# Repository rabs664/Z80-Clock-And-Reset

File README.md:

# Z80-Clock-And-Reset
Simple 555 based astable and monostable clock and reset board.

The Z80 Clock and Reset board provides a variable astable clock where the frequency can be controlled by R8 or a monostable clock to allow the clock to be "single-stepped". The switch S1 toggles between the astable and monostable clock. Additional the switch S3 provides a reset signal for use with the Z80. 

Astable Clock Output

## Objective
Support Z80 CPU learning, specifically used with associated Z80 CPU Boards.

## Background
Used extensively during early Z80 learning to single step the clock or slow run the clock and watch the Z80 activity.

## Testing
The Z80 Clock and Reset V1.2 board has been built and tested. 

## PCBs
Gerber files are available in Code.

## Components
This [Digi-Key List](https://www.digikey.co.uk/en/mylists/list/MAI0B51H04) contains all components.

## Resources
[Zed80 Website](http://zed80.com/Z80-RETRO/index_Home.html)

[Ben Eater Clock](https://eater.net/8bit/clock)

## Acknowledgements
Don Prefontaine 

Peter Murray

[Ben Eater](https://eater.net)

# Release History
## Version 1.2
* First Release

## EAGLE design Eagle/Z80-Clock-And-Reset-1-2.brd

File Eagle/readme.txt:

This folder contains the Eagle Schematic, Board and Gerber output files.

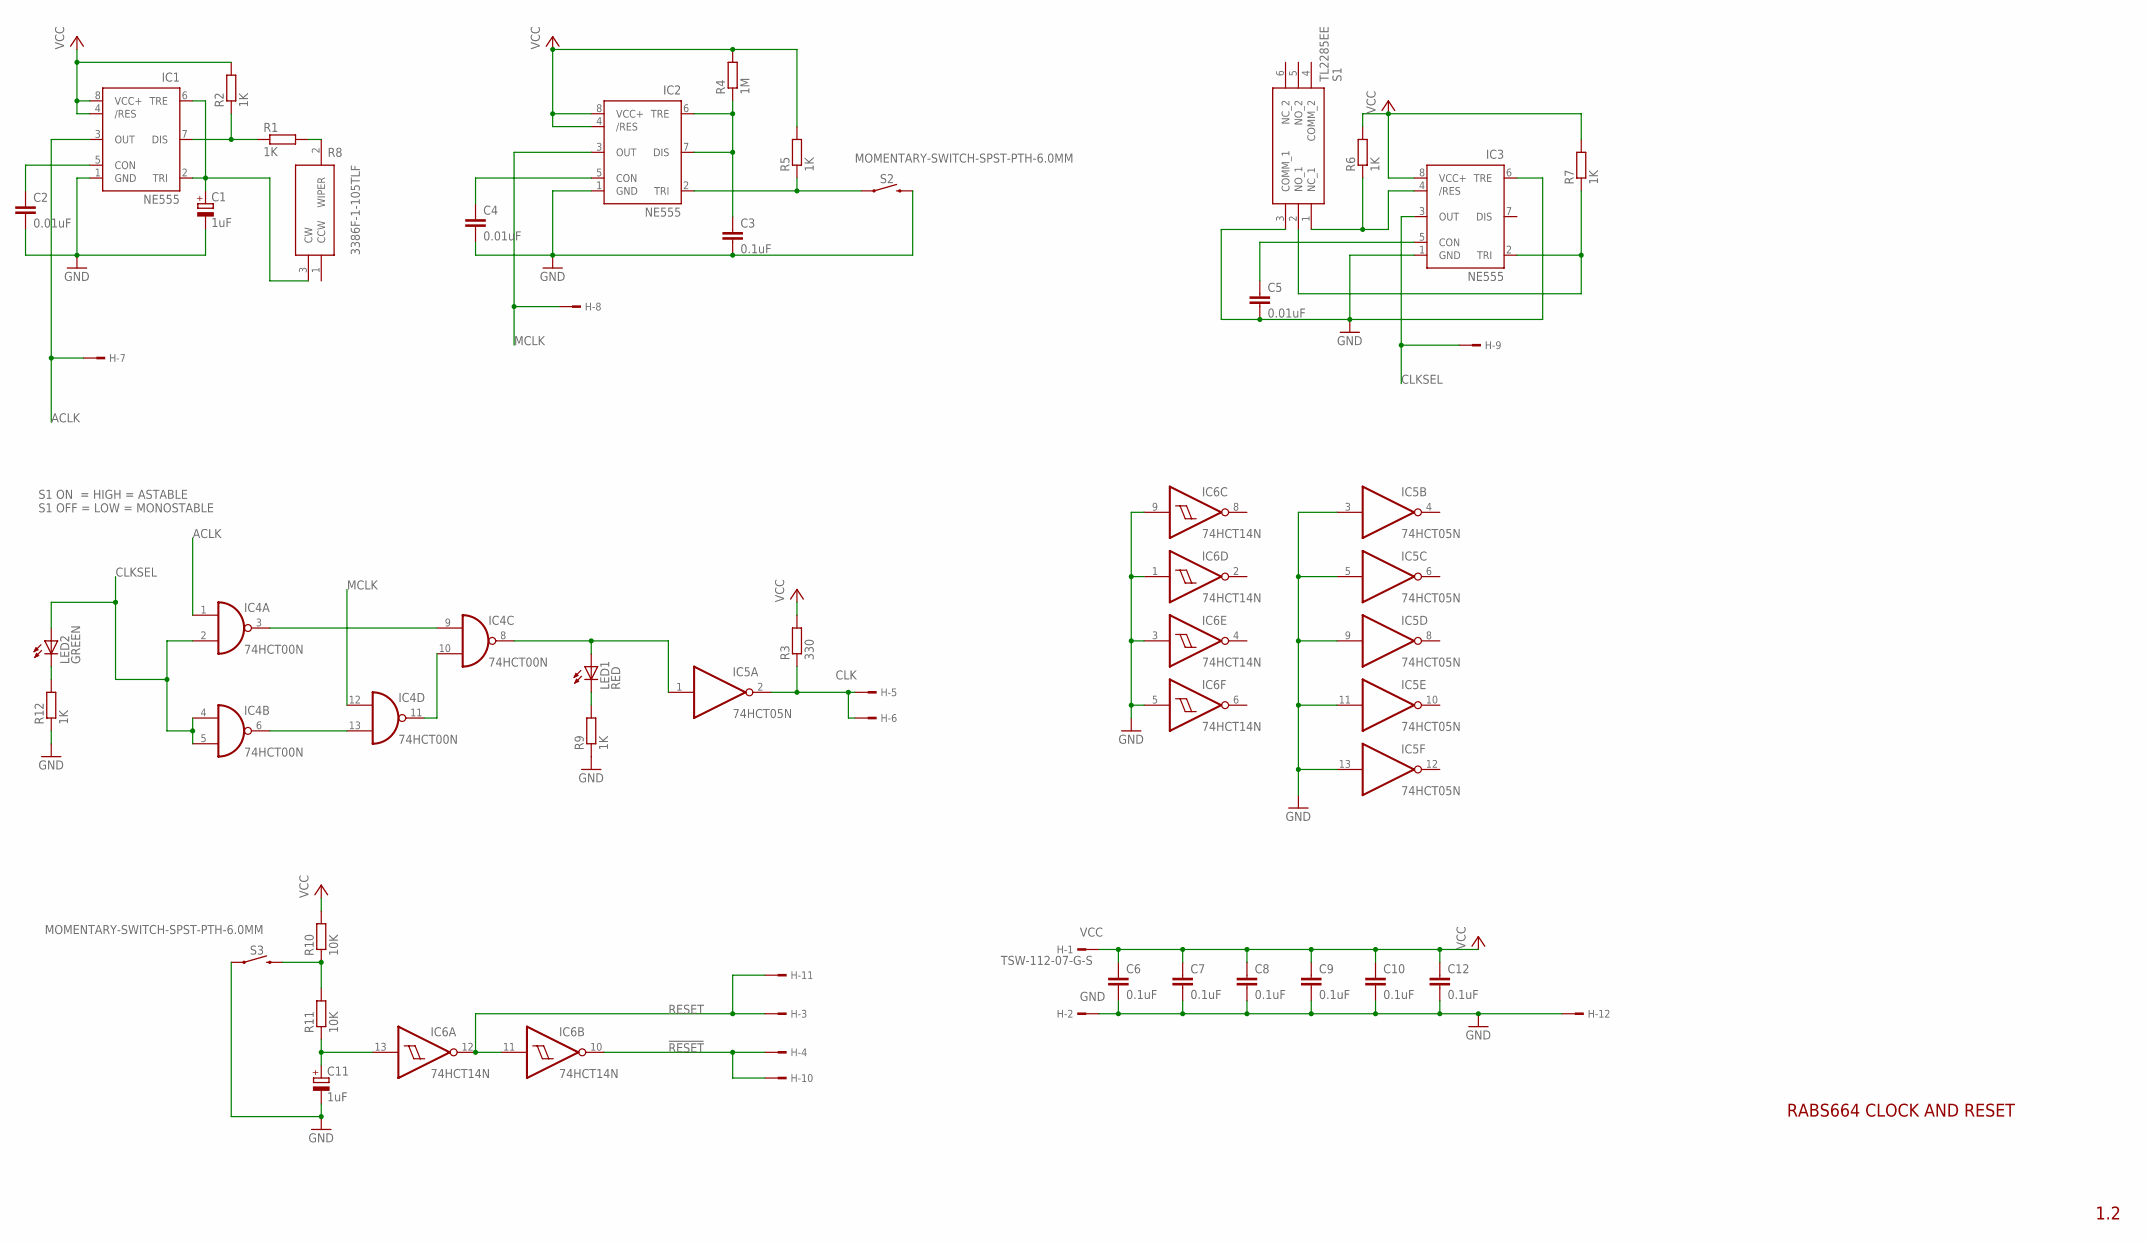
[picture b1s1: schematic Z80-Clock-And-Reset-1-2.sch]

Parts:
C1, C11: 1uF; E2,5-6E
C2, C4, C5: 0.01uF; C050-025X075
C3, C6, C7, C8, C9, C10, C12: 0.1uF; C050-025X075
H: TSW-112-07-G-S; TSW-112-XX-G-S
IC1, IC2, IC3: NE555; DIL-08
IC4: 74HCT00N; DIL14
IC5: 74HCT05N; DIL14
IC6: 74HCT14N; DIL14
LED1: RED; LED3MM
LED2: GREEN; LED3MM
R1, R2, R5, R6, R7, R9, R12: 1K; 0207/10
R3: 330; 0207/10
R4: 1M; 0207/10
R8: 3386F-1-103TLF; 3386F1103TLF
R10, R11: 10K; 0207/10
S1: TL2285EE
S2, S3: MOMENTARY-SWITCH-SPST-PTH-6.0MM; TACTILE_SWITCH_PTH_6.0MM

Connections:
!RESET: H.4, H.10, IC6.10 (O)
ACLK: H.7, IC1.3 (OUT), IC4.1 (I0)
CLK: H.5, H.6, IC5.2 (O), R3.1
CLKSEL: H.9, IC3.3 (OUT), IC4.2 (I1), IC4.4 (I0), IC4.5 (I1), LED2.A
GND: C1.-, C2.2, C3.2, C4.2, C5.2, C6.2, C7.2, C8.2, C9.2, C10.2, C11.-, C12.2, H.2, H.12, IC1.1 (GND), IC2.1 (GND), IC3.1 (GND), IC3.6 (TRE), IC4.7 (GND), IC5.3 (I), IC5.5 (I), IC5.7 (GND), IC5.9 (I), IC5.11 (I), IC5.13 (I), IC6.1 (I), IC6.3 (I), IC6.5 (I), IC6.7 (GND), IC6.9 (I), R9.1, R12.1, S1.3 (COMM_1), S2.3 (2), S3.1
MCLK: H.8, IC2.3 (OUT), IC4.12 (I0)
unnamed: C2.1, IC1.5 (CON)
unnamed: C1.+, IC1.2 (TRI), IC1.6 (TRE), R8.3 (CW)
unnamed: IC1.7 (DIS), R1.1, R2.1
unnamed: IC3.4 (/RES), R6.1, S1.1 (NC_1)
unnamed: R1.2, R8.2 (WIPER)
unnamed: C3.1, IC2.6 (TRE), IC2.7 (DIS), R4.1
unnamed: C4.1, IC2.5 (CON)
unnamed: IC2.2 (TRI), R5.1, S2.1
unnamed: LED2.K (C), R12.2
unnamed: IC4.3 (O), IC4.9 (I0)
unnamed: C5.1, IC3.5 (CON)
unnamed: IC4.6 (O), IC4.13 (I1)
unnamed: IC3.2 (TRI), R7.1, S1.2 (NO_1)
unnamed: IC4.10 (I1), IC4.11 (O)
unnamed: IC4.8 (O), IC5.1 (I), LED1.A
unnamed: LED1.K (C), R9.2
unnamed: R10.1, R11.2, S3.3 (2)
unnamed: C11.+, IC6.13 (I), R11.1
RESET: H.3, H.11, IC6.11 (I), IC6.12 (O)
VCC: C6.1, C7.1, C8.1, C9.1, C10.1, C12.1, H.1, IC1.4 (/RES), IC1.8 (VCC+), IC2.4 (/RES), IC2.8 (VCC+), IC3.8 (VCC+), IC4.14 (VCC), IC5.14 (VCC), IC6.14 (VCC), R2.2, R3.2, R4.2, R5.2, R6.2, R7.2, R10.2

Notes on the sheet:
RABS664 CLOCK AND RESET
1.2
3386F-1-105TLF
S1 ON = HIGH = ASTABLE S1 OFF = LOW = MONOSTABLE

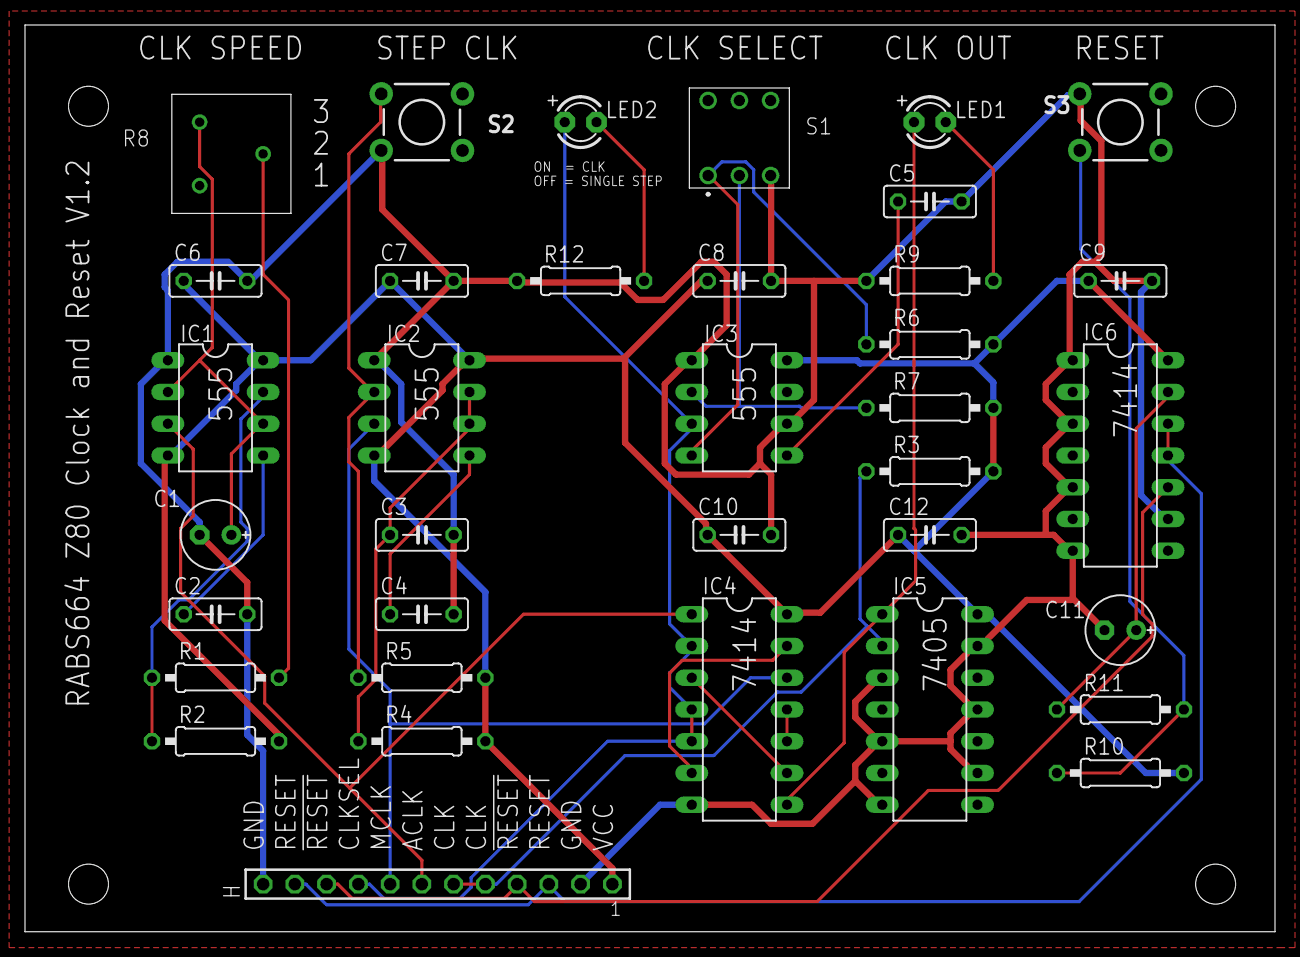
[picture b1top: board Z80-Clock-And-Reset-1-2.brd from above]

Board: 2 copper layers, 100.0 x 72.5 mm, 36 parts (0 on the bottom side), 26 nets.

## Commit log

2023-06-13 Create BOM
2024-11-11 Update README.md
    Update PIC of board to version 1.2 and remove references to private projects.
2024-11-11 Add PDF of schematic

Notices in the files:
parts and their libraries:
SparkFun-Switches: Licensing: Creative Commons ShareAlike 4.0 International - https://creativecommons.org/licenses/by-sa/4.0
